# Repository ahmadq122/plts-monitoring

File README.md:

# PLTS Monitoring
A monitoring device for solar power plants
This device can read data from the solar panel system, measure current and voltage, and store data using microSD card media. 
In addition, the device has a user interface to display the measured data using an LCD 20x04.

## The block diagram of the solar power system monitoring system, including sensors, microcontroller, and user interface is as follows:

## Description of how the device works in general:
This tool will measure the voltage value generated by a solar panel and the DC electric current that is being flowed.
The measurement results will then be recorded in a certain time interval into a file document in a Micro SD card.

## The type of sensor that will be used to measure the current and voltage of the solar panel:
Current Sensor: ACS712
Voltage Sensor: ACPL-C87B

## Reasons for selecting the sensor:
ACS712
- Output voltage proportional to AC or DC currents
- Low-noise analog signal path
- Commonly used sensor and small output error 1.5% at Ambient temp 25C
- 
ACPL-C87B
- Isolated DC-bus voltage sensing
- High accuracy
- 0.1% non-linearity max
- 

## Schematic and PCB design using EDA application (Kicad):
- Please check kicad folder

## Create source code for the microcontroller (AVR ATmega 328p)
- Please check firmware folder

## Simulate the device design using the Proteus application:
- Please check proteus folder

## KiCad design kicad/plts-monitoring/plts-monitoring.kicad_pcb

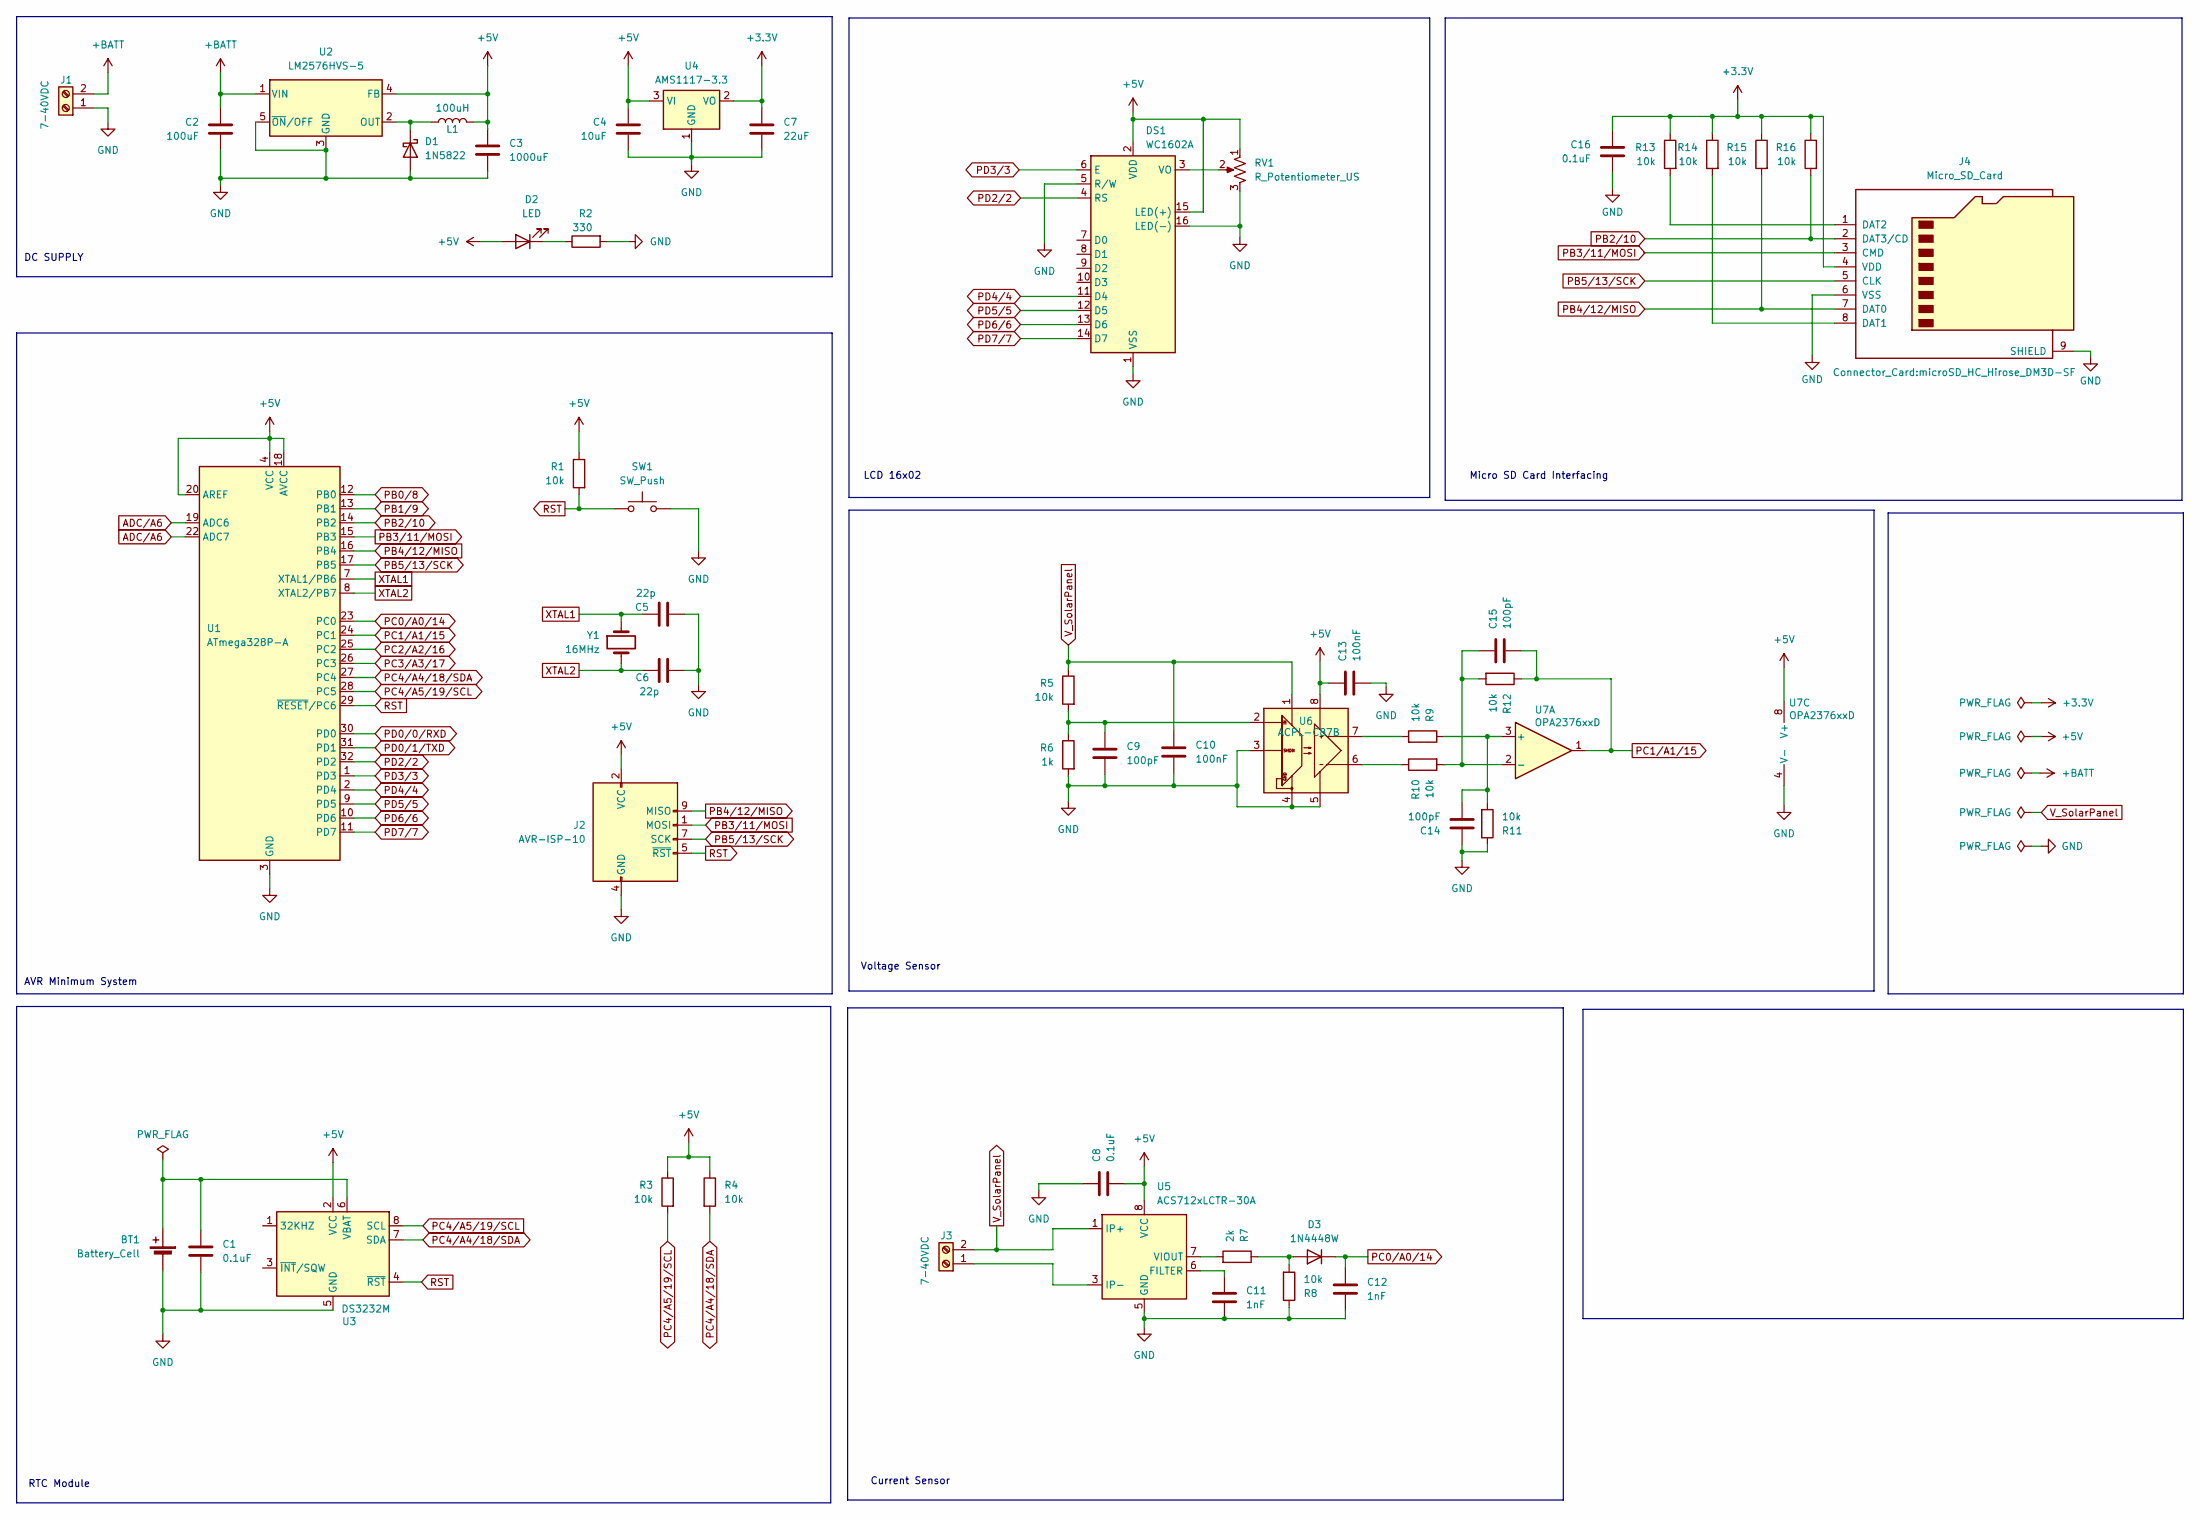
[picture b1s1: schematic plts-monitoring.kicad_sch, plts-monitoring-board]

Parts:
BT1: Battery_Cell; BatteryHolder_Keystone_3000_1x12mm
C1, C8: 0.1uF; CP_EIA-1608-10_AVX-L
C2: 100uF; CP_Elec_5x5.7
C3: 1000uF; CP_Elec_5x5.7
C4: 10uF; CP_EIA-2012-12_Kemet-R
C5, C6: 22p; C_0805_2012Metric
C7: 22uF; CP_EIA-2012-12_Kemet-R
C9, C14, C15: 100pF; CP_EIA-1608-10_AVX-L
C10, C13: 100nF; CP_EIA-1608-10_AVX-L
C11, C12: 1nF; CP_EIA-1608-10_AVX-L
C16: 0.1uF; CP_EIA-2012-12_Kemet-R
D1: 1N5822; D_DO-201AD_P15.24mm_Horizontal
D2: LED; LED_0805_2012Metric
D3: 1N4448W; D_SOD-123
DS1: WC1602A
J1, J3: 7-40VDC; TerminalBlock_Phoenix_MKDS-1,5-2-5.08_1x02_P5.08mm_Horizont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
J2: AVR-ISP-10; IDC-Header_2x05_P2.54mm_Vertical
J4: Micro_SD_Card; microSD_HC_Hirose_DM3D-SF
L1: 100uH; L_Bourns_SRP7028A_7.3x6.6mm
R1, R3, R4, R5, R8, R9, R10, R11, R12, R13, R14, R15, R16: 10k; R_0805_2012Metric
R2: 330; R_0805_2012Metric
R6: 1k; R_0805_2012Metric
R7: 2k; R_0805_2012Metric
RV1: R_Potentiometer_US; Potentiometer_Bourns_3224X_Vertical
SW1: SW_Push; SW_PUSH_6mm_H4.3mm
U1: ATmega328P-A; TQFP-32_7x7mm_P0.8mm
U2: LM2576HVS-5; TO-263-5_TabPin3
U3: DS3232M; SOIC-8_3.9x4.9mm_P1.27mm
U4: AMS1117-3.3; SOT-223-3_TabPin2
U5: ACS712xLCTR-30A; SOIC-8_3.9x4.9mm_P1.27mm
U6: ACPL-C87B; SSO-8_6.8x5.9mm_P1.27mm_Clearance8mm
U7: OPA2376xxD; TSSOP-8_3x3mm_P0.65mm
Y1: 16MHz; Crystal_SMD_2012-2Pin_2.0x1.2mm

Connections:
+3.3V: C7.1, C16.1, J4.4 (VDD), R13.1, R14.1, R15.1, R16.1, U4.2 (VO)
+5V: C3.1, C4.1, C8.2, C13.1, D2.2 (A), DS1.2 (VDD), DS1.15 (LED(+)), J2.2 (VCC), L1.2, R1.1, R3.1, R4.1, RV1.1, U1.4 (VCC), U1.6 (VCC), U1.18 (AVCC), U1.20 (AREF), U2.4 (FB), U3.2 (VCC), U4.3 (VI), U5.8 (VCC), U6.8 (VDD2), U7.8 (V+)
+BATT: C2.1, J1.2, U2.1 (VIN)
ADC/A6: U1.19 (ADC6), U1.22 (ADC7)
GND: BT1.2 (-), C1.2, C2.2, C3.2, C4.2, C5.2, C6.1, C7.2, C8.1, C9.2, C10.2, C11.2, C12.2, C13.2, C14.1, C16.2, D1.2 (A), DS1.1 (VSS), DS1.5 (R/W), DS1.16 (LED(-)), J1.1, J2.4 (GND), J2.6 (GND), J2.8 (GND), J2.10 (GND), J4.6 (VSS), J4.9 (SHIELD), R2.2, R6.2, R8.1, R11.1, RV1.3, SW1.2, U1.3 (GND), U1.5 (GND), U1.21 (GND), U2.3 (GND), U2.5 (~ON/OFF), U3.5 (GND), U4.1 (GND), U5.5 (GND), U6.3 (IN-), U6.4 (GND1), U6.5 (GND2), U7.4 (V-)
unnamed: BT1.1 (+), C1.1, U3.6 (VBAT)
unnamed: D1.1 (K), L1.1, U2.2 (OUT)
unnamed: D2.1 (K), R2.1
unnamed: D3.2 (A), R7.1, R8.2
unnamed: DS1.3 (VO), RV1.2
unnamed: J3.1, U5.3 (IP-), U5.4 (IP-)
unnamed: J4.8 (DAT1), R14.2
unnamed: J4.1 (DAT2), R13.2
unnamed: C11.1, U5.6 (FILTER)
unnamed: R7.2, U5.7 (VIOUT)
unnamed: C9.1, R5.2, R6.1, U6.2 (IN)
unnamed: R9.2, U6.7 (OUT+)
unnamed: R10.1, U6.6 (OUT-)
unnamed: C14.2, R9.1, R11.2, U7.3 (+)
unnamed: C15.1, R10.2, R12.2, U7.2 (-)
PB0/8: U1.12 (PB0)
PB1/9: U1.13 (PB1)
PB2/10: J4.2 (DAT3/CD), R16.2, U1.14 (PB2)
PB3/11/MOSI: J2.1 (MOSI), J4.3 (CMD), U1.15 (PB3)
PB4/12/MISO: J2.9 (MISO), J4.7 (DAT0), R15.2, U1.16 (PB4)
PB5/13/SCK: J2.7 (SCK), J4.5 (CLK), U1.17 (PB5)
PC0/A0/14: C12.1, D3.1 (K), U1.23 (PC0)
PC1/A1/15: C15.2, R12.1, U1.24 (PC1), U7.1
PC2/A2/16: U1.25 (PC2)
PC3/A3/17: U1.26 (PC3)
PC4/A4/18/SDA: R4.2, U1.27 (PC4), U3.7 (SDA)
PC4/A5/19/SCL: R3.2, U1.28 (PC5), U3.8 (SCL)
PD0/0/RXD: U1.30 (PD0)
PD0/1/TXD: U1.31 (PD1)
PD2/2: DS1.4 (RS), U1.32 (PD2)
PD3/3: DS1.6 (E), U1.1 (PD3)
PD4/4: DS1.11 (D4), U1.2 (PD4)
PD5/5: DS1.12 (D5), U1.9 (PD5)
PD6/6: DS1.13 (D6), U1.10 (PD6)
PD7/7: DS1.14 (D7), U1.11 (PD7)
RST: J2.5 (~RST), R1.2, SW1.1, U1.29 (~RESET/PC6), U3.4 (~RST)
V_SolarPanel: C10.1, J3.2, R5.1, U5.1 (IP+), U5.2 (IP+), U6.1 (VDD1)
XTAL1: C5.1, U1.7 (XTAL1/PB6), Y1.1
XTAL2: C6.2, U1.8 (XTAL2/PB7), Y1.2

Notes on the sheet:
LCD 16x02
RTC Module
DC SUPPLY
Current Sensor
Voltage Sensor
Micro SD Card Interfacing
AVR Minimum System

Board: 2 copper layers, 52 parts (0 on the bottom side), 38 nets, no tracks yet.

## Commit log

2024-01-21 Create folder tree & Diagram block of the system
2024-01-21 Add initial source folder tree
2024-01-21 Update README.md
    Added block diagram of the system
2024-01-21 Update all materials for hardware design
2024-01-22 Add source code, Proteus simulation
2024-01-23 Update sources: - MachineEnum and MachineData
2024-01-24 New class for sensor and fixed wrong constraint limit of in MachineData
2024-01-24 Add function RTC, SD, LCD and Data Logging
2024-01-24 Default max current value 20A, add kicad project
2024-01-24 Add Micro SD Card footprint
2024-01-25 Add moving average function for sensor ADC reading
2024-01-25 Remove moving avg func due 2 mem limit, improve memory efficiency instead
2024-01-25 Fixed Data Time not showing on the LCD
2024-01-25 Update KiCad schematic
2024-01-25 Update schematic to pass ERC and some footprints
